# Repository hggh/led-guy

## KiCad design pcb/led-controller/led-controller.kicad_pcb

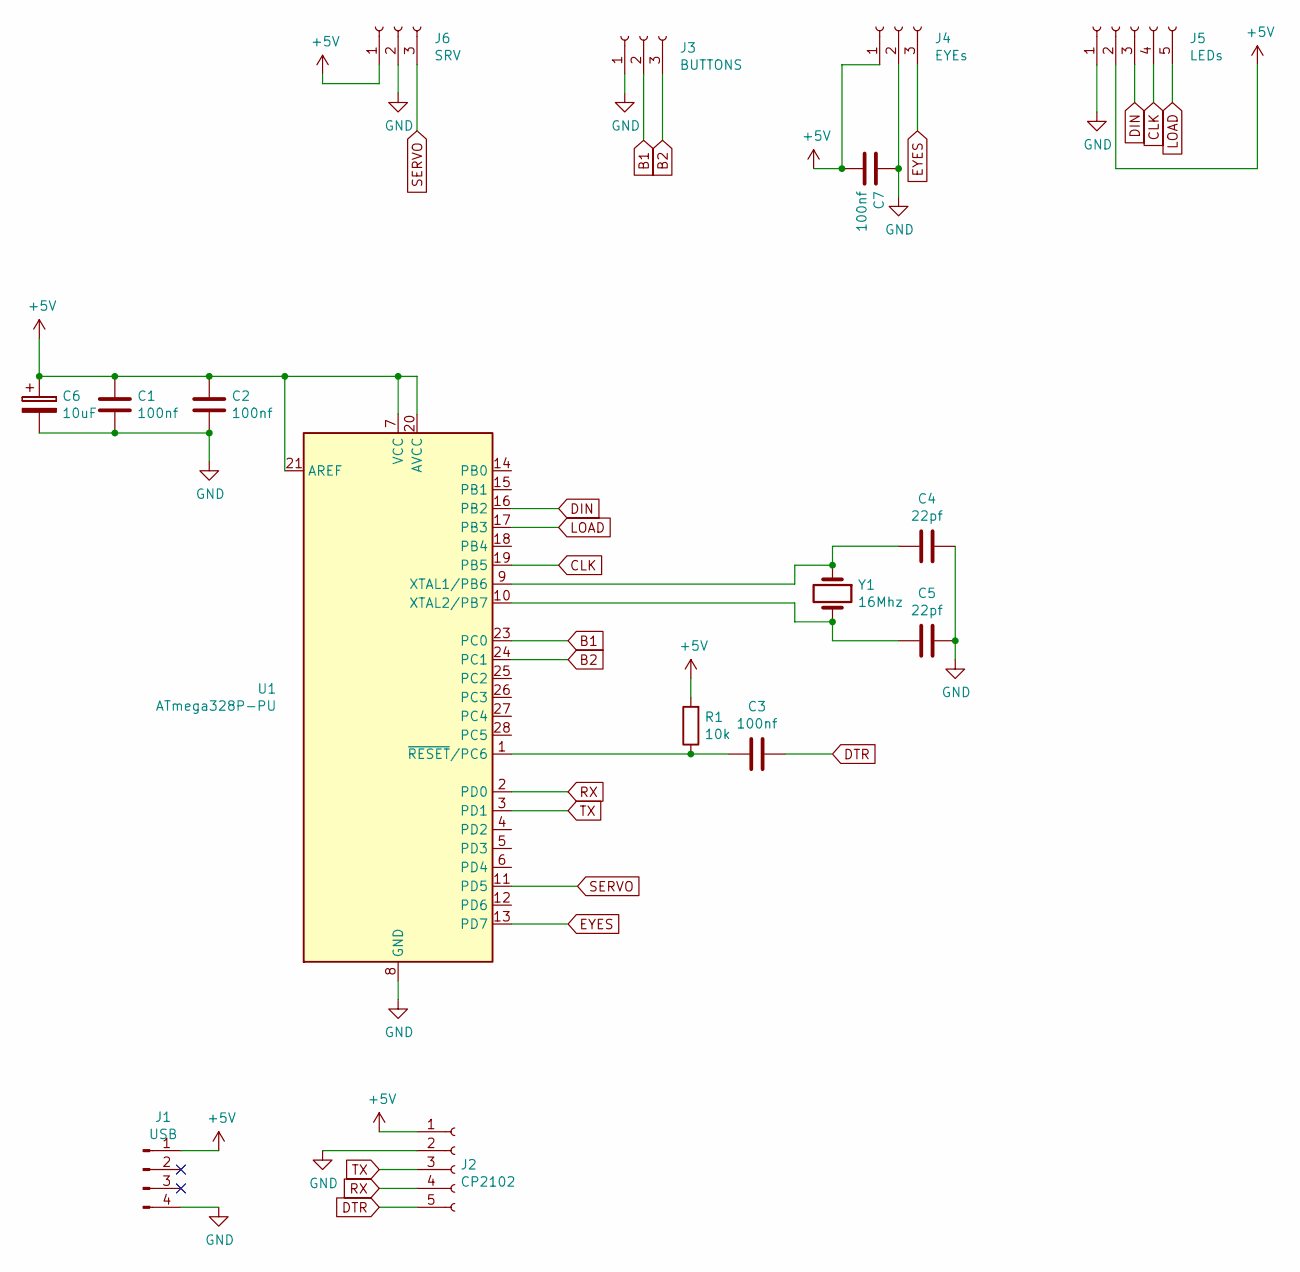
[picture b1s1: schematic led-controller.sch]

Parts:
C1, C2, C3, C7: 100nf; C_0805_2012Metric
C4, C5: 22pf; C_0805_2012Metric
C6: 10uF; CP_Radial_D4.0mm_P2.00mm
J1: USB; PinHeader_1x04_P2.54mm_Vertical
J2: CP2102; PinHeader_1x05_P2.54mm_Vertical
J3: BUTTONS; PinHeader_1x03_P2.54mm_Vertical
J4: EYEs; PinHeader_1x03_P2.54mm_Vertical
J5: LEDs; PinHeader_1x05_P2.54mm_Vertical
J6: SRV; PinHeader_1x03_P2.00mm_Vertical
R1: 10k; R_0805_2012Metric
U1: ATmega328P-PU; DIP-28_W7.62mm_Socket_LongPads
Y1: 16Mhz; Crystal_HC49-U_Vertical

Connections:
+5V: C1.1, C2.1, C6.1, C7.2, J1.1, J2.1, J4.1, J5.2, J6.1, R1.2, U1.7 (VCC), U1.20 (AVCC), U1.21 (AREF)
B1: J3.2, U1.23 (PC0)
B2: J3.3, U1.24 (PC1)
CLK: J5.4, U1.19 (PB5)
DIN: J5.3, U1.16 (PB2)
DTR: C3.1, J2.5
EYES: J4.3, U1.13 (PD7)
GND: C1.2, C2.2, C4.1, C5.1, C6.2, C7.1, J1.4, J2.2, J3.1, J4.2, J5.1, J6.2, U1.8 (GND), U1.22 (GND)
LOAD: J5.5, U1.17 (PB3)
unnamed: C3.2, R1.1, U1.1 (~RESET~/PC6)
unnamed: C4.2, U1.9 (XTAL1/PB6), Y1.1
unnamed: C5.2, U1.10 (XTAL2/PB7), Y1.2
RX: J2.4, U1.2 (PD0)
SERVO: J6.3, U1.11 (PD5)
TX: J2.3, U1.3 (PD1)

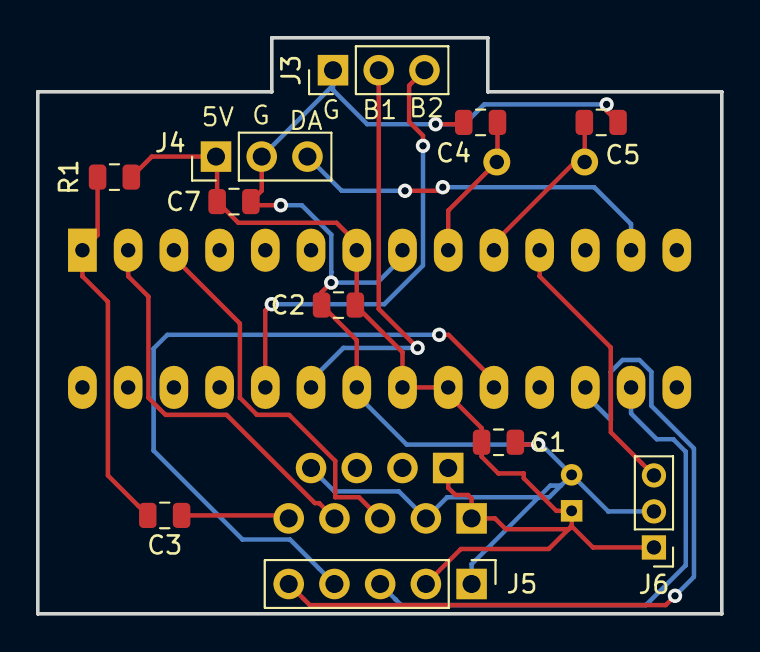
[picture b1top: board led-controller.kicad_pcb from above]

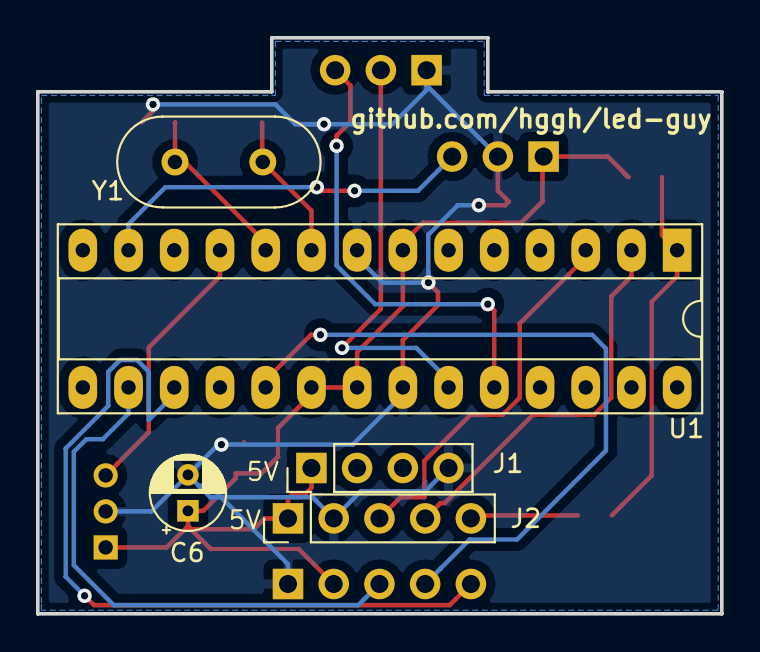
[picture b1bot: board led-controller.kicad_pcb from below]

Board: 2 copper layers, 38.0 x 32.0 mm, 16 parts (5 on the bottom side), 15 nets.

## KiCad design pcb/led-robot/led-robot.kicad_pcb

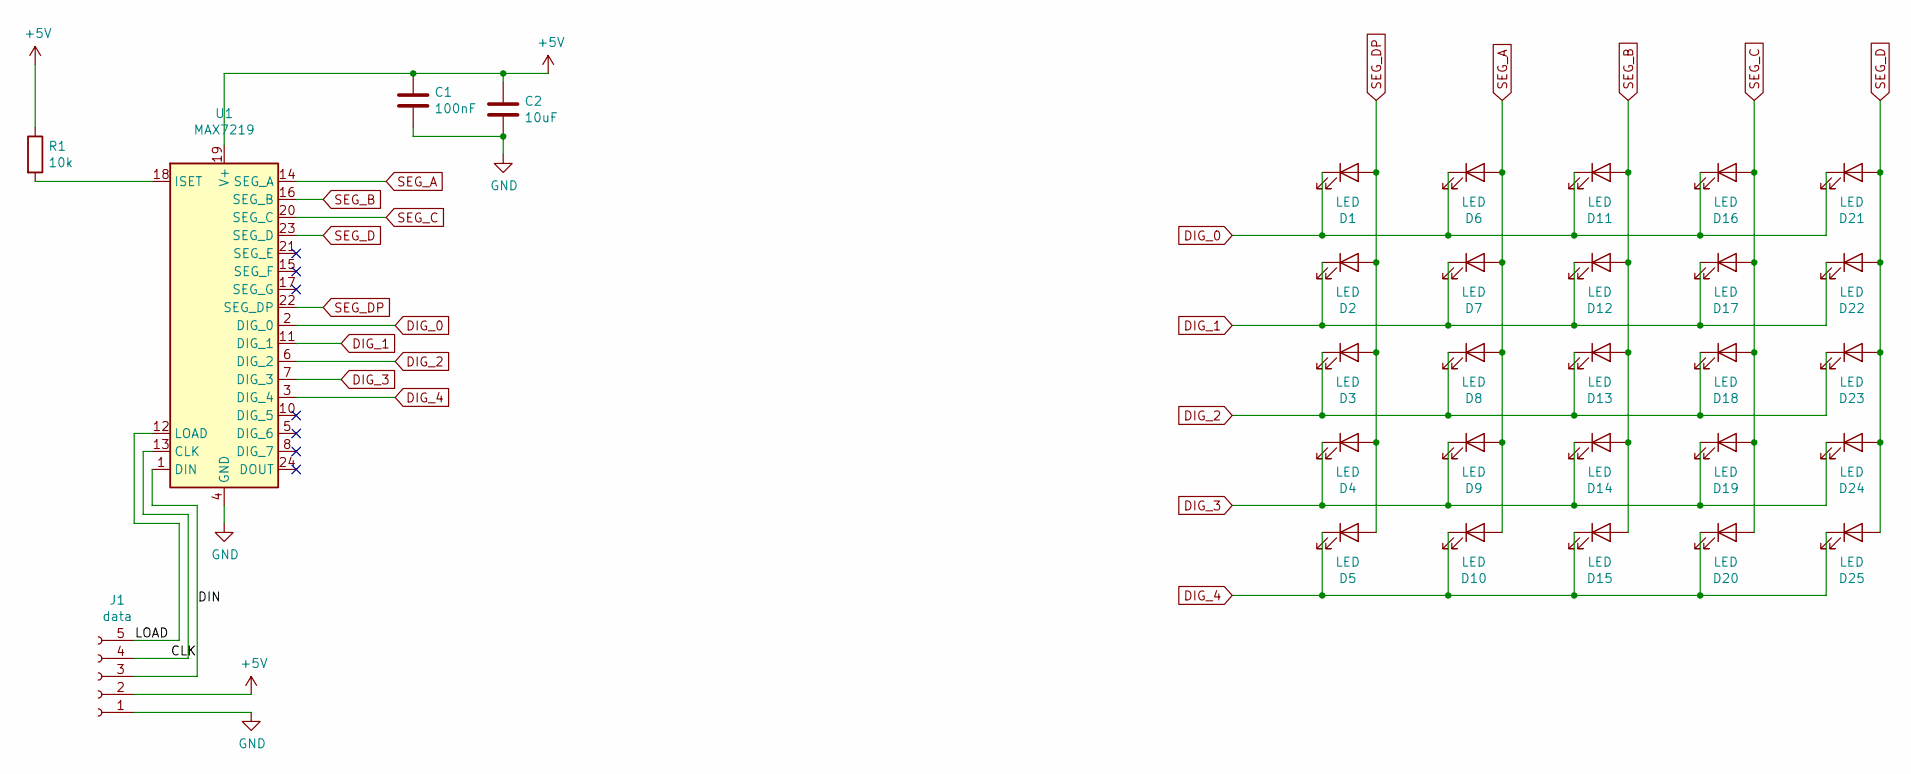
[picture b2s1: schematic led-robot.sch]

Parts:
C1: 100nF; C_0805_2012Metric
C2: 10uF; C_0805_2012Metric
D1, D2, D3, D4, D5, D6, D7, D8, D9, D10, D11, D12, D13, D14, D15, D16, D17, D18, D19, D20, D21, D22, D23, D24, D25: LED; LED_0805_2012Metric
J1: data; PinHeader_1x05_P2.54mm_Vertical
R1: 10k; R_0805_2012Metric
U1: MAX7219; SOIC-24W_7.5x15.4mm_P1.27mm

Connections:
+5V: C1.1, C2.1, J1.2, R1.1, U1.19 (V+)
/CLK: J1.4, U1.13 (CLK)
/DIN: J1.3, U1.1 (DIN)
/LOAD: J1.5, U1.12 (LOAD)
DIG_0: D1.1 (K), D6.1 (K), D11.1 (K), D16.1 (K), D21.1 (K), U1.2 (DIG_0)
DIG_1: D2.1 (K), D7.1 (K), D12.1 (K), D17.1 (K), D22.1 (K), U1.11 (DIG_1)
DIG_2: D3.1 (K), D8.1 (K), D13.1 (K), D18.1 (K), D23.1 (K), U1.6 (DIG_2)
DIG_3: D4.1 (K), D9.1 (K), D14.1 (K), D19.1 (K), D24.1 (K), U1.7 (DIG_3)
DIG_4: D5.1 (K), D10.1 (K), D15.1 (K), D20.1 (K), D25.1 (K), U1.3 (DIG_4)
GND: C1.2, C2.2, J1.1, U1.4 (GND), U1.9 (GND)
unnamed: R1.2, U1.18 (ISET)
SEG_A: D6.2 (A), D7.2 (A), D8.2 (A), D9.2 (A), D10.2 (A), U1.14 (SEG_A)
SEG_B: D11.2 (A), D12.2 (A), D13.2 (A), D14.2 (A), D15.2 (A), U1.16 (SEG_B)
SEG_C: D16.2 (A), D17.2 (A), D18.2 (A), D19.2 (A), D20.2 (A), U1.20 (SEG_C)
SEG_D: D21.2 (A), D22.2 (A), D23.2 (A), D24.2 (A), D25.2 (A), U1.23 (SEG_D)
SEG_DP: D1.2 (A), D2.2 (A), D3.2 (A), D4.2 (A), D5.2 (A), U1.22 (SEG_DP)

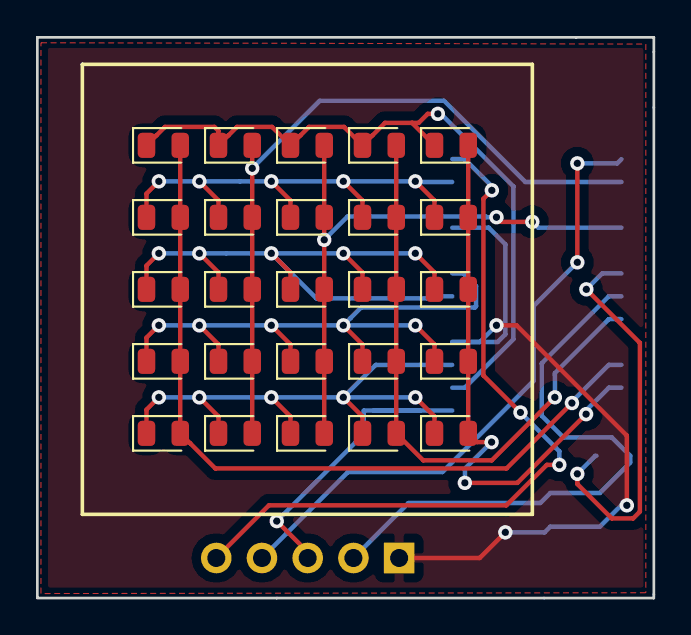
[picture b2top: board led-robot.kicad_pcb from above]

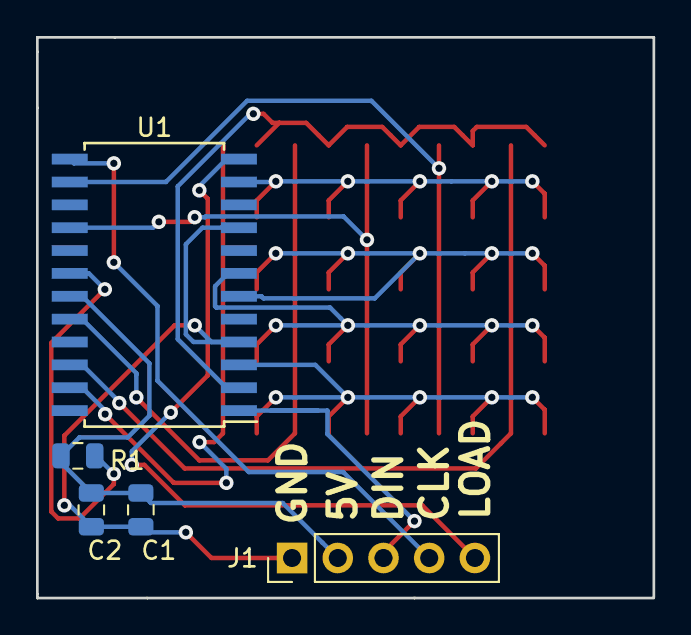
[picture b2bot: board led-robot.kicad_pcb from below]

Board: 2 copper layers, 34.2 x 31.2 mm, 30 parts (5 on the bottom side), 16 nets.

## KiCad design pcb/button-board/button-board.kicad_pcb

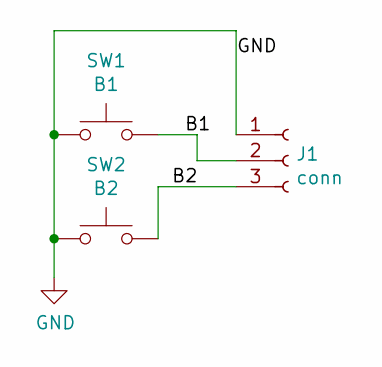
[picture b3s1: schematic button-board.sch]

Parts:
J1: conn; PinHeader_1x03_P2.54mm_Vertical
SW1: B1; SMD_Button
SW2: B2; SMD_Button

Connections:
/B1: J1.2, SW1.2
/B2: J1.3, SW2.2
GND: J1.1, SW1.1, SW2.1

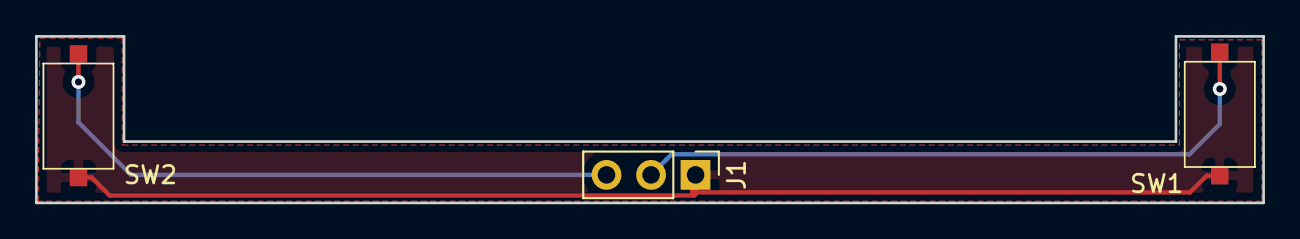
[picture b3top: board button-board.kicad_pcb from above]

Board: 2 copper layers, 70.0 x 9.5 mm, 3 parts (0 on the bottom side), 3 nets.

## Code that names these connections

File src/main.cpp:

#include <Arduino.h>
#include <MAX7219_8x8_matrix.h>

#include <FastLED.h>
#include <Bounce2.h>

#include "chars.h"

#define NUM_LEDS 2
#define EYE_PIN 7
#define BUTTON1_PIN A0
#define BUTTON2_PIN A1

/*
 * 1 = display message
 * 2 = display stars
 */
uint8_t matrix_mode = 1;
CRGB eyes[NUM_LEDS];
uint8_t eyes_color_index = 1;
unsigned long eyes_start_time = 0;
unsigned long eyes_interval_time = 40;

unsigned long matrix_start_time = 0;
unsigned long matrix_interval_time = 0;
bool message_same_char = false;

Button b1 = Button();
Button b2 = Button();

// LOAD = 11 = CS == PB3 Pin 17
// CLK = 13 = CLK  == PB5 Pin19
// DIN = 10 = DATA == PB2 Pin16
MAX7219_8x8_matrix LEDmatrix(10,11,13);

const uint8_t messages_size = 3;
String messages[messages_size] = {
  String("alles gute zum geburtstag"),
  String("frohes neues jahr"),
  String("du bist toll!"),
};
String message_personal = String("hallo zusammen!");
String message_special = String("hallo zusammen!");
String message = message_personal;
unsigned int message_index = 0;
unsigned int current_messages_index = 0;

const static CRGB::HTMLColorCode colors[35] = {
  CRGB::Crimson,
  CRGB::Red,
  CRGB::DeepPink,
  CRGB::OrangeRed,
  CRGB::SkyBlue,
  CRGB::Orange,
  CRGB::Gold,
  CRGB::Yellow,
  CRGB::DarkRed,
  CRGB::Violet,
  CRGB::Navy,
  CRGB::Fuchsia,
  CRGB::RosyBrown,
  CRGB::MediumOrchid,
  CRGB::BlueViolet,
  CRGB::Indigo,
  CRGB::DarkSlateBlue,
  CRGB::GreenYellow,
  CRGB::Purple,
  CRGB::Lime,
  CRGB::MediumSpringGreen,
  CRGB::ForestGreen,
  CRGB::CadetBlue,
  CRGB::DarkGreen,
  CRGB::LightSeaGreen,
  CRGB::Teal,
  CRGB::Cyan,
  CRGB::SteelBlue,
  CRGB::Blue,
  CRGB::Brown,
  CRGB::DarkBlue,
  CRGB::Chocolate,
  CRGB::SaddleBrown,
  CRGB::Maroon,
  CRGB::DarkSlateGray
};

void print_char(char c) {
  uint8_t *matrix;
  switch (c) {
    case 'a':
      matrix = char_5x5_A;
      break;
    case 'b':
      matrix = char_5x5_B;
      break;
    case 'c':
      matrix = char_5x5_C;
      break;
    case 'd':
      matrix = char_5x5_D;
      break;
    case 'e':
      matrix = char_5x5_E;
      break;
    case 'f':
      matrix = char_5x5_F;
      break;
    case 'g':
      matrix = char_5x5_G;
      break;
    case 'h':
      matrix = char_5x5_H;
      break;
    case 'i':
      matrix = char_5x5_I;
      break;
    case 'j':
      matrix = char_5x5_J;
      break;
    case 'k':
      matrix = char_5x5_K;
      break;
    case 'l':
      matrix = char_5x5_L;
      break;
    case 'm':
      matrix = char_5x5_M;
      break;
    case 'n':
      matrix = char_5x5_N;
      break;
    case 'o':
      matrix = char_5x5_O;
      break;
    case 'p':
      matrix = char_5x5_P;
      break;
    case 'q':
      matrix = char_5x5_Q;
      break;
    case 'r':
      matrix = char_5x5_R;
      break;
    case 's':
      matrix = char_5x5_S;
      break;
    case 't':
      matrix = char_5x5_T;
      break;
    case 'u':
      matrix = char_5x5_U;
      break;
    case 'v':
      matrix = char_5x5_V;
      break;
    case 'w':
      matrix = char_5x5_W;
      break;
    case 'x':
      matrix = char_5x5_X;
      break;
    case 'y':
      matrix = char_5x5_Y;
      break;
    case 'z':
      matrix = char_5x5_Z;
      break;
    case '!':
      matrix = char_5x5_EXCLA;
      break;
    case ' ':
      matrix = char_5x5_WHITESPACE;
      break;
  }
  LEDmatrix.setBrightness(0);
  LEDmatrix.matrix(matrix);
}

void clear() {
  LEDmatrix.clear();
}

void setup() {
  Serial.begin(9600);

  b1.attach(BUTTON1_PIN, INPUT_PULLUP);
  b1.interval(25);
  b1.setPressedState(LOW);

  b2.attach(BUTTON2_PIN, INPUT_PULLUP);
  b2.interval(25);
  b2.setPressedState(LOW);

  LEDmatrix.clear();
  LEDmatrix.setBrightness(0);

  FastLED.addLeds<NEOPIXEL, EYE_PIN>(eyes, NUM_LEDS);
  FastLED.setBrightness(5);

  randomSeed(analogRead(0));

  LEDmatrix.matrix(char_5x5_EXCLA);
  delay(200);
  clear();
  delay(75);
  LEDmatrix.matrix(char_5x5_EXCLA);
  delay(100);
  LEDmatrix.matrix(char_5x5_EXCLA);
  delay(100);
  clear();
}

void set_matrix_interval_time(unsigned long t) {
  matrix_interval_time = t;
  matrix_start_time = millis();
}

void print_message() {
  message.toLowerCase();
  if (message_index != 0 && message.charAt(message_index) == message.charAt(message_index - 1)) {
    if (message_same_char == false) {
      message_same_char = true;
      // if the next char is the same as current clear the display for some time
      clear();
      set_matrix_interval_time(400);
      return;
    }
  }
  else {
    message_same_char = false;
  }
  print_char(message.charAt(message_index));
  message_index++;
  set_matrix_interval_time(650);
  return;
}

void print_stars() {
  uint8_t stars[8] = {
    (uint8_t)random(0, 248),
    (uint8_t)random(0, 248),
    (uint8_t)random(0, 248),
    (uint8_t)random(0, 248),
    (uint8_t)random(0, 248),
    0,
    0,
    0
  };
  LEDmatrix.setBrightness(random(0, 3));
  LEDmatrix.matrix(stars);
  set_matrix_interval_time(random(500, 1500));
}

void loop() {
  b1.update();
  b2.update();

  if (b2.pressed()) {
    // right button
    message = message_special;
    message_index = 0;
    matrix_mode = 1;
    matrix_start_time = 0;
  }

  if (b1.pressed()) {
    // left button
    message = messages[current_messages_index];
    message_index = 0;
    matrix_mode = 1;
    matrix_start_time = 0;

    current_messages_index++;
    if (current_messages_index > messages_size) {
      current_messages_index = 0;
    }
  }

  if (millis() - eyes_start_time >= eyes_interval_time) {
    eyes_start_time = millis();
    eyes_color_index = random(0, 35);
    eyes_interval_time = random(800, 1400);
    FastLED.setBrightness(random(4, 30));

    fill_solid(eyes, NUM_LEDS, colors[eyes_color_index]);
    if ( millis() % 4 == 0) {
      eyes[1] = colors[random(0, 35)];
    }
    FastLED.show();
  }

  if (matrix_mode == 1) {
    if (millis() - matrix_start_time >= matrix_interval_time) {
      print_message();
    }
    // we reach the end of the string..
    if (message_index == message.length()) {
      message_index = 0;

      // jump to mode 2
      matrix_mode = 2;
    }
  }

  // Mode: Stars
  if (matrix_mode == 2) {
    if (millis() - matrix_start_time >= matrix_interval_time) {
      print_stars();
    }
  }
}

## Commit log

2020-08-08 add pcb
2020-08-08 update pcb
2020-09-10 add old matrix led library
2020-09-10 initial version with eye colors and text message
2020-09-11 add pic
2020-09-11 print text with non blocking version
2020-09-11 add stars
2020-09-15 update size
2020-09-16 update pcb to fit spacing inside MDF
2020-09-16 add 328p DIP controller with Servo, 2x push switch and MAX led
2020-09-16 add push button pcb
2020-09-16 make the pcb a litter bigger
2020-09-17 update final pcb
2020-09-17 Add Bounce2 for Buttons
2020-10-02 add usb holder
2020-10-02 add whitespace
2020-10-02 add more text and buttons
2020-10-08 fix buttons and random messages
2020-12-20 new holder for 90° angle usb port, arms will not break again
2020-12-20 print messages in a row and start from begin; no random
2021-02-06 add no/simle icons
2021-05-30 add question mark
